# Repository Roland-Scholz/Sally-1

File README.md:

# Sally-1
Reengineering &amp; Repair RSD GmbH Sally-1 Floppy-Controller and CP/M System for Atari 8-Bit

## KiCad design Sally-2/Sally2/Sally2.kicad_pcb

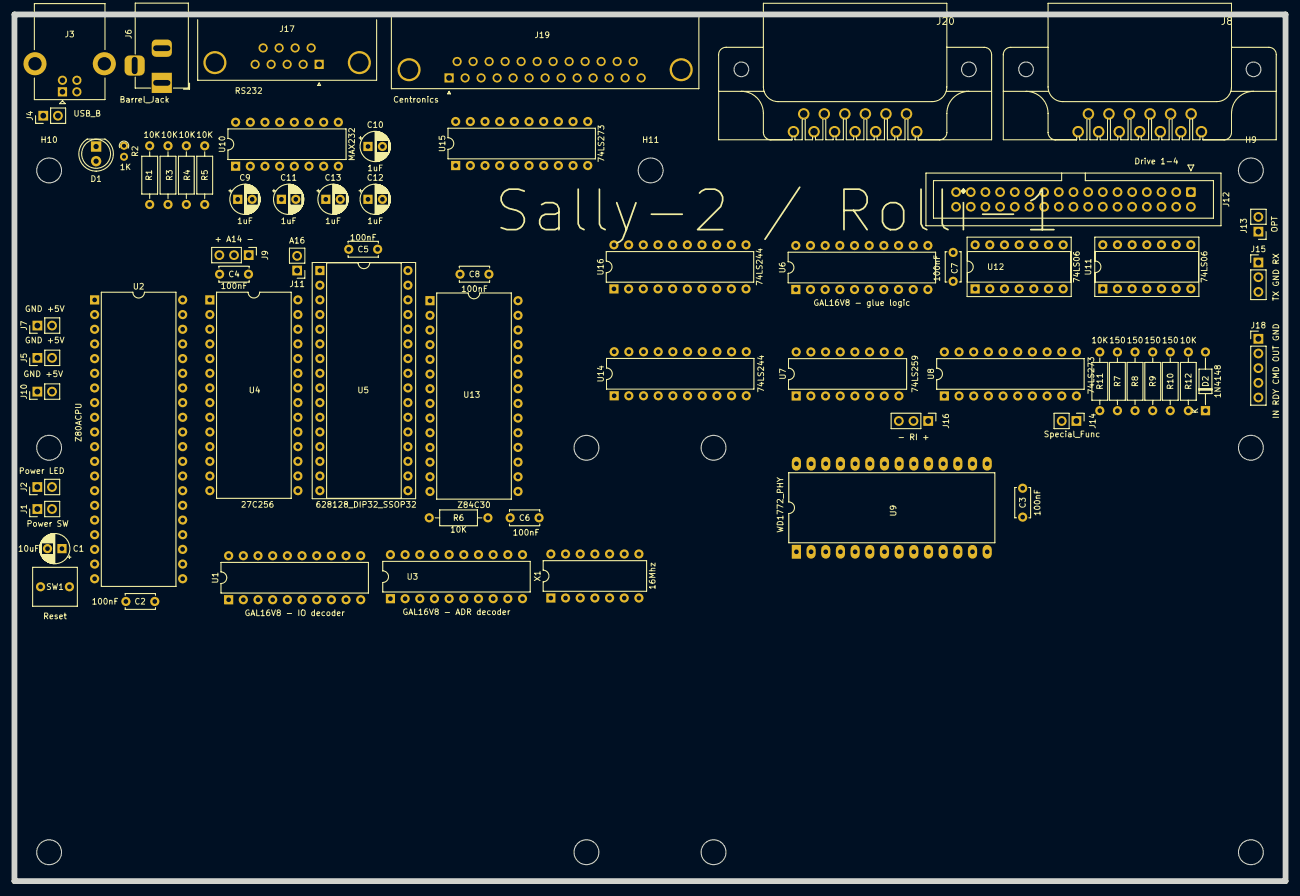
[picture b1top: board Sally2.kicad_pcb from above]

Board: 2 copper layers, 220.0 x 150.0 mm, 76 parts (0 on the bottom side), 143 nets, no tracks yet.

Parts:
C1: 10uF; CP_Radial_D5.0mm_P2.50mm
C2, C3, C4, C5, C6, C7, C8: 100nF; C_Disc_D5.0mm_W2.5mm_P5.00mm
C9, C10, C11, C12, C13: 1uF; CP_Radial_D5.0mm_P2.50mm
D1: LD271; LED_D5.0mm_IRGrey
D2: 1N4148; D_DO-35_SOD27_P10.16mm_Horizontal
H1, H2, H3, H4, H5, H6, H7, H8, H9, H10, H11: MountingHole; MountingHole_4.3mm_M4
J1: Power SW; PinHeader_1x02_P2.54mm_Vertical
J2: Power LED; PinHeader_1x02_P2.54mm_Vertical
J3: USB_B; USB_B_Lumberg_2411_02_Horizontal
J4: PowerIn; PinHeader_1x02_P2.54mm_Vertical
J5, J7, J10: GND +5V; PinHeader_1x02_P2.54mm_Vertical
J6: Barrel_Jack; BarrelJack_Horizontal
J8, J20: Conn_01x13; SIO_JACK
J9: + A14 -; PinHeader_1x03_P2.54mm_Vertical
J11: A16; PinHeader_1x02_P2.54mm_Vertical
J12: Drive 1-4; IDC-Header_2x17_P2.54mm_Vertical
J13: OPT; PinHeader_1x02_P2.54mm_Vertical
J14: Special_Func; PinHeader_1x02_P2.54mm_Vertical
J15: TX GND RX; PinHeader_1x03_P2.54mm_Vertical
J16: - RI +; PinHeader_1x03_P2.54mm_Vertical
J17: RS232; DSUB-9_Male_Horizontal_P2.77x2.84mm_EdgePinOffset4.94mm_Hou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
J18: IN RDY CMD OUT GND; PinHeader_1x05_P2.54mm_Vertical
J19: Centronics; DSUB-25_Female_Horizontal_P2.77x2.84mm_EdgePinOffset7.70mm_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
R1, R3, R4, R5, R6, R11, R12: 10K; R_Axial_DIN0207_L6.3mm_D2.5mm_P10.16mm_Horizontal
R2: 1K; R_Axial_DIN0204_L3.6mm_D1.6mm_P1.90mm_Vertical
R7, R8, R9, R10: 150; R_Axial_DIN0207_L6.3mm_D2.5mm_P10.16mm_Horizontal
SW1: Reset; C_Rect_L7.5mm_W6.5mm_P5.00mm
U1: GAL16V8 - IO decoder; DIP-20_W7.62mm
U2: Z80ACPU; DIP-40_W15.24mm
U3: GAL16V8 - ADR decoder; DIP-20_W7.62mm
U4: 27C256; DIP-28_W15.24mm
U5: 628128_DIP32_SSOP32; DIP-32_W15.24mm_Socket
U6: GAL16V8 - glue logic; DIP-20_W7.62mm
U7: 74LS259; DIP-16_W7.62mm
U8, U15: 74LS273; DIP-20_W7.62mm
U9: WD1772_PHY; DIP-28_W15.24mm_LongPads
U10: MAX232; DIP-16_W7.62mm
U11, U12: 74LS06; DIP-14_W7.62mm_Socket
U13: Z84C30; DIP-28_W15.24mm
U14, U16: 74LS244; DIP-20_W7.62mm
X1: 16Mhz; DIP-14_W7.62mm

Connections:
+5V: C2.1, C3.1, C4.1, C5.1, C6.1, C7.1, C8.1, C10.1, C12.2, J1.1, J5.2, J7.2, J9.3, J10.2, J16.1, R1.1, R2.1, R3.1, R4.1, R5.1, R6.1, R7.1, R8.1, R9.1, R10.1, R11.2, R12.1, U1.20 (VCC), U2.11 (VCC), U3.20 (VCC), U4.1 (VPP), U4.28 (VCC), U5.30 (CS2), U5.32 (VCC), U6.20 (VCC), U7.16 (VCC), U8.20 (VCC), U9.15 (Vcc), U10.16 (VCC), U11.14 (VCC), U12.14 (VCC), U13.24 (VCC), U14.20 (VCC), U15.20 (VCC), U16.20 (VCC), X1.14 (Vcc)
/A2: U2.32 (A2), U4.8 (A2), U5.10 (A2), U7.3 (A2)
/A3: U2.33 (A3), U4.7 (A3), U5.9 (A3)
/A4: U1.1 (I1/CLK), U2.34 (A4), U4.6 (A4), U5.8 (A4)
/A5: U1.2 (I2), U2.35 (A5), U4.5 (A5), U5.7 (A5)
/A6: U1.3 (I3), U2.36 (A6), U4.4 (A6), U5.6 (A6)
/A7: U1.4 (I4), U2.37 (A7), U4.3 (A7), U5.5 (A7)
/A8: U2.38 (A8), U4.25 (A8), U5.27 (A8)
/A9: U2.39 (A9), U4.24 (A9), U5.26 (A9)
/A10: U2.40 (A10), U4.21 (A10), U5.23 (A10)
/A11: U2.1 (A11), U4.23 (A11), U5.25 (A11)
/A12: U2.2 (A12), U4.2 (A12), U5.4 (A12)
/A13: U2.3 (A13), U4.26 (A13), U5.28 (A13)
/A14: U2.4 (A14), U5.3 (A14)
/A15: U2.5 (A15), U3.4 (I4), U5.31 (A15)
/IO/P0: J19.2, U15.2 (Q0)
/IO/P1: J19.3, U15.5 (Q1)
/IO/P2: J19.4, U15.6 (Q2)
/IO/P3: J19.5, U15.9 (Q3)
/IO/P4: J19.6, U15.12 (Q4)
/IO/P5: J19.7, U15.15 (Q5)
/IO/P6: J19.8, U15.16 (Q6)
/IO/P7: J19.9, U15.19 (Q7)
/SIO1: J8.1, J20.1
/SIO2: J8.2, J20.2
/SIO3: J8.3, J20.3
/SIO5: J8.5, J20.5
/SIO7: J8.7, J20.7
/SIO8: J8.8, J20.8
/SIO9: J8.9, J20.9
/SIO10: J8.10, J20.10
/SIO11: J8.11, J20.11
/SIO12: J8.12, J20.12
/SIO13: J8.13, J20.13
A0: U2.30 (A0), U4.10 (A0), U5.12 (A0), U7.1 (A0), U9.3 (A0), U13.18 (CS0)
A1: U2.31 (A1), U4.9 (A1), U5.11 (A1), U7.2 (A1), U9.4 (A1), U13.19 (CS1)
A14IN: J9.2, U4.27 (A14)
ACK: J19.10, U16.11 (I0b)
ATDAT: U6.2 (I2), U7.4 (Q0)
ATDAT_OUT: D2.1 (K), U6.19 (IO1)
BITW\: U1.14 (IO6), U7.14 (E)
BUSY: J19.11, U16.17 (I3b)
B\S: U3.7 (I7), U8.12 (Q4)
CLK4: U2.6 (~CLK), U3.18 (IO2), U13.15 (CLK)
CLK16: U3.1 (I1/CLK), U3.9 (I9), X1.8 (OUT)
CMDSIO: U6.8 (I8), U7.12 (Q7)
CTCCE: U1.16 (IO4), U13.16 (~CE)
CTS: U10.12 (R1OUT), U14.8 (I3a)
D0: U2.14 (D0), U4.11 (D0), U5.13 (Q0), U7.13 (D), U8.14 (D5), U9.5 (DAL0), U13.25 (D0), U15.3 (D0)
D1: U2.15 (D1), U4.12 (D1), U5.14 (Q1), U8.3 (D0), U9.6 (DAL1), U13.26 (D1), U14.12 (O3a), U15.4 (D1), U16.16 (O1a)
D2: U2.12 (D2), U4.13 (D2), U5.15 (Q2), U8.18 (D7), U9.7 (DAL2), U13.27 (D2), U14.14 (O2a), U15.7 (D2)
D3: U2.8 (D3), U4.15 (D3), U5.17 (Q3), U8.17 (D6), U9.8 (DAL3), U13.28 (D3), U14.16 (O1a), U15.8 (D3), U16.12 (O3a)
D4: U2.7 (D4), U4.16 (D4), U5.18 (Q4), U8.4 (D1), U9.9 (DAL4), U13.1 (D4), U15.13 (D4), U16.9 (O0b)
D5: U2.9 (D5), U4.17 (D5), U5.19 (Q5), U8.8 (D3), U9.10 (DAL5), U13.2 (D5), U15.14 (D5), U16.7 (O1b)
D6: U2.10 (D6), U4.18 (D6), U5.20 (Q6), U8.13 (D4), U9.11 (DAL6), U13.3 (D6), U15.17 (D6), U16.5 (O2b)
D7: U2.13 (D7), U4.19 (D7), U5.21 (Q7), U8.7 (D2), U9.12 (DAL7), U13.4 (D7), U14.18 (O0a), U15.18 (D7), U16.3 (O3b), U16.18 (O0a)
DRQ: U6.3 (I3), U9.27 (DRQ)
DSEL1: J12.10, U11.6
DSEL2: J12.12, U11.2
DSEL3: J12.14, U11.10
DSEL4: J12.6, U11.8
DSKDIR\: J12.18, U12.2
DSKIP\: J12.8, R7.2, U14.11 (I0b)
DSKRD\: J12.30, R10.2, U14.17 (I3b)
DSKSTEP\: J12.20, U12.4
DSKTRK00\: J12.26, R8.2, U14.13 (I1b)
DSKWD\: J12.22, U12.8
DSKWG\: J12.24, U12.6
DSKWP\: J12.28, R9.2, U14.15 (I2b)
DSW\: U1.15 (IO5), U8.11 (Cp)
DTR: U7.10 (Q5), U10.11 (T1IN)
FDCCE\: U1.17 (I03), U9.1 (~CS)
FDCCLK: U3.14 (IO6), U9.18 (CLK)
FDCRD: U9.19 (~RD), U14.3 (O3b)
FDCRES: U3.5 (I5), U8.5 (Q1)
GND: C1.2, C2.2, C3.2, C4.2, C5.2, C6.2, C7.2, C8.2, C10.2, C13.1, D1.1 (K), J2.1, J3.4 (GND), J4.1, J5.1, J6.2, J7.1, J8.4, J8.6, J9.1, J10.1, J11.2, J12.1, J12.3, J12.5, J12.7, J12.9, J12.11, J12.13, J12.15, J12.17, J12.19, J12.21, J12.23, J12.25, J12.27, J12.29, J12.31, J12.33, J13.2, J14.2, J15.2, J16.3, J17.5, J18.1, J19.17, J19.18, J19.19, J19.20, J19.21, J19.22, J19.23, J19.24, J19.25, J20.4, J20.6, SW1.1, U1.10 (GND), U2.29 (GND), U3.10 (GND), U3.11 (I10/~OE), U4.14 (GND), U5.16 (GND), U6.10 (GND), U6.11 (I10/~OE), U7.8 (GND), U8.10 (GND), U9.14 (GND), U10.15 (GND), U11.7 (GND), U12.7 (GND), U13.5 (GND), U14.10 (GND), U14.19 (OEb), U15.10 (GND), U16.10 (GND), X1.7 (GND)
HALT\: U2.18 (~HALT), U6.5 (I5)
INTRQ: U6.4 (I4), U9.28 (INTRQ)
INT\: R3.2, U2.16 (~INT), U13.12 (~INT)
IORQ\: U1.5 (I5), U2.20 (~IORQ), U13.10 (~IORQ)
IP\: U9.24 (~IP), U14.9 (O0b)
M1\: U1.8 (I8), U2.27 (~M1), U13.14 (~M1)
MEMRQ\: U2.19 (~MREQ), U3.2 (I2)
MO: U9.20 (MO), U11.13
MOTOR: J12.16, U11.12
NMI\: U2.17 (~NMI), U6.18 (IO2)
unnamed: D1.2 (A), J2.2, R2.2
unnamed: J1.2, J3.1 (VBUS), J4.2, J6.1
unnamed: J11.1, U5.2 (A16)
unnamed: J12.2, J13.1
unnamed: J14.1, R11.1, U14.4 (I1a)
unnamed: R1.2, U2.25 (~BUSRQ)
unnamed: U8.2 (Q0), U11.1
unnamed: U8.9 (Q3), U11.3
unnamed: U8.15 (Q5), U11.5
unnamed: U8.16 (Q6), U11.9
unnamed: U8.19 (Q7), U11.11
unnamed: U9.17 (DIRC), U12.1
unnamed: U9.16 (STEP), U12.3
unnamed: U9.22 (WD), U12.9
unnamed: U9.21 (WG), U12.5
unnamed: C9.1, U10.1 (C1+)
unnamed: C9.2, U10.3 (C1-)
unnamed: C11.1, U10.4 (C2+)
unnamed: C11.2, U10.5 (C2-)
unnamed: C12.1, U10.2 (VS+)
unnamed: C13.2, U10.6 (VS-)
unnamed: U13.9 (ZC/TO2), U13.20 (CLK/TRG3)
unnamed: R6.2, U13.13 (IEI)
PE: J19.12, U16.15 (I2b)
PRTR\: U1.19 (IO1), U16.19 (OEb)
PRTW\: U1.18 (IO2), U15.11 (Cp)
RAMCE\: U3.17 (I03), U5.22 (~CS1)
RD\: U1.6 (I6), U2.21 (~RD), U4.22 (~OE), U5.24 (~OE), U13.6 (~RD)
RESC\: U2.26 (~RESET), U3.12 (IO8), U7.15 (Clr), U8.1 (~Mr), U13.17 (~RESET), U15.1 (~Mr)
RES\: C1.1, R5.2, SW1.2, U3.6 (I6)
RI: J16.2, U14.6 (I2a)
ROMCE\: U3.16 (IO4), U4.20 (~CE)
ROMENA\: U3.3 (I3), U7.6 (Q2)
RS232R\: U1.13 (IO7), U14.1 (OEa)
RS232_CTS: J17.8, U10.13 (R1IN)
RS232_DTR: J17.4, U10.14 (T1OUT)
RS232_RX: J17.2, U10.8 (R2IN)
RS232_TX: J17.3, U10.7 (T2OUT)
RX: J15.1, U10.9 (R2OUT), U13.21 (CLK/TRG2), U14.2 (I0a)
SDDD\: U8.6 (Q2), U9.26 (~DDEN)
SEL: J19.13, U16.13 (I1b)
SIDE: J12.32, U11.4
SIOCMD: J18.3, U6.7 (I7), U16.4 (I1a)
SIOIN: D2.2 (A), J18.5, R12.2
SIOOUT: J18.2, U6.6 (I6), U16.2 (I0a)
SIORDY: J18.4, U16.8 (I3a)
SIOR\: U1.12 (IO8), U16.1 (OEa)
STROBE: U3.8 (I8), U7.7 (Q3)
STROBE\: J19.1, U3.13 (IO7)
TO1: U6.1 (I1/CLK), U13.8 (ZC/TO1)
TR00\: U9.23 (~TR00), U14.7 (O1b)
TRG0: U6.17 (I03), U13.23 (CLK/TRG0)
TX: J15.3, U7.5 (Q1), U10.10 (T2IN)
WAIT\: R4.2, U2.24 (~WAIT)
WDRES\: U3.15 (IO5), U9.13 (~MR)
WPRT\: U9.25 (~WPRT), U14.5 (O2b)
WR\: U1.7 (I7), U2.22 (~WR), U5.29 (~WE), U9.2 (R/~W)

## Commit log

2024-02-29 comments
2024-08-04 Rolli
2024-08-31 better SallyConv.java
2024-08-31 percom descr
2024-09-07 workover part 1
2025-04-15 autoterm+move to Sally2
